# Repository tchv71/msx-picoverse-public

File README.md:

# PicoVerse for MSX

**The MSX experience driven by the Raspberry Pi Pico family of microcontrollers.**

PicoVerse is a community-driven effort to build versatile MSX cartridges powered by Raspberry Pi Pico development boards. The project pairs accessible hardware designs with ready-to-flash firmware so MSX users can jump straight into loading games, tools, and Nextor without having to compile sources.

| Cartridge Label - 2040 Variant | Cartridge Label - 2350 Variant |
|---------|---------|
| |  |

PicoVerse is designed as an open-source, independent, and documented MSX cartridge platform. Compatibility with other projects is neither a goal nor guaranteed (I tested some without much success); running third‑party software on PicoVerse hardware, or PicoVerse firmware on other boards, is at your own risk. The source and manufacturing files are openly available so you can learn, experiment, and build on them for the MSX community, subject to the project license.

If you find any issues, have questions, or want to contribute, please open an issue or reach out via the contact information in the repository.

## Project Highlights

- Single-ROM LoadROM workflow for instant and easy booting of one title.
- Multi-ROM loader with an on-screen menu and mapper auto-detection.
- Explorer firmware (PicoVerse 2350) merges flash and microSD ROMs, labels the source (FL/SD), adds MP3 playback, supports on-device search, includes ROM detail audio profiles with SCC/SCC+ and Dual PSG support, and includes an integrated File Hunter browser for downloading ROMs over ESP-01 WiFi.
- Ready-made Nextor builds with USB pendrive (`-s2`/`-m2`) or microSD card (`-s1`/`-m1`) via Sunrise IDE emulation on PicoVerse 2350, and USB (`-s`/`-m`) on PicoVerse 2040.
- Sunrise IDE + 192KB memory mapper on PicoVerse 2040 (`loadrom.exe -m`), or Sunrise IDE standalone (`loadrom.exe -s`).
- Sunrise IDE + 1MB PSRAM memory mapper on PicoVerse 2350 (`loadrom.exe -m1` for microSD, `loadrom.exe -m2` for USB), or Sunrise IDE standalone (`loadrom.exe -s1` / `loadrom.exe -s2`).
- Carnivore2-compatible RAM-mode loader on PicoVerse 2350 (`loadrom.exe -c1` / `loadrom.exe -c2`) for `SROM.COM /D15` uploads into the 1MB PSRAM mapper.
- ESP-01 WiFi support for PicoVerse 2350 Sunrise IDE LoadROM/MultiROM builds (`loadrom.exe -s1 -w`, `-m1 -w`, `-s2 -w`, `-m2 -w`) and for the Explorer File Hunter browser. Compatible with both real MSX hardware and FPGA-based MSX cores.
- SCC/SCC+, Dual PSG, and MSX-MUSIC/YM2413 emulation on the PicoVerse 2350, with per-ROM audio profile selection where supported.
- PC-side tooling that generates UF2 images locally for quick drag-and-drop flashing.
- USB keyboard support on PicoVerse 2040 — use a standard USB keyboard as the MSX keyboard via the cartridge slot.
- MSX-MIDI support on PicoVerse 2040 — use a USB-MIDI cable as a standard MSX-MIDI interface via the cartridge slot. 
- MIDI-PAC support on PicoVerse 2040 — passively convert live MSX PSG music and effects into high-quality MIDI for external synths or sound modules (SC-55 optimized). Features automatic bass detection, tone+noise coexistence, smooth pitch bending on fast passages, and improved percussion mapping. 
- USB joystick support on PicoVerse 2040 — plug a standard USB gamepad (HID, Xbox 360, Xbox One, or Xbox Series X|S) into the USB-C port and it appears as one or two native MSX joysticks with no MSX-side software needed. Uses open-drain bus driving to coexist with the real PSG.
- BOMs, and production-ready Gerbers.
- Active development roadmap covering RP2040 and RP2350-based cartridges.

## Documentation

**LoadROM Guides:** Use the LoadROM tool to create a UF2 image that boots directly into a single ROM, skipping the menu. Mapper type is auto-detected with filename tag overrides, and the tool reports the detected configuration before flashing.
- [MSX PicoVerse 2040 LoadROM Tool Manual (English)](/docs/msx-picoverse-2040-loadrom-tool-manual.en-us.md) 
- [MSX PicoVerse 2350 LoadROM Tool Manual (English)](/docs/msx-picoverse-2350-loadrom-tool-manual.en-us.md) 
  
**MultiROM Guides:** Use the MultiROM tool to create a UF2 image that allows selecting from multiple ROMs at boot. Mapper type is auto-detected with filename tag overrides, and the tool reports the detected configuration before flashing.
- [PicoVerse 2040 MultiROM Guide Manual (English)](/docs/msx-picoverse-2040-multirom-tool-manual.en-us.md)
- [PicoVerse 2350 MultiROM Tool Manual (English)](/docs/msx-picoverse-2350-multirom-tool-manual.en-us.md)

**Explorer Guides:** Use the Explorer tool to manage flash and microSD ROMs, play MP3s, browse File Hunter over ESP-01 WiFi, and search for titles on the device.
- [MSX PicoVerse 2350 Explorer Tool Manual (English)](/docs/msx-picoverse-2350-explorer-tool-manual.en-us.md)

**Reference Material** 
- [PicoVerse 2040 Features Overview](/docs/msx-picoverse-2040-features.md)
- [PicoVerse 2350 Features Overview](/docs/msx-picoverse-2350-features.md)
- [MSX PicoVerse 2350 Dual PSG Implementation](/docs/msx-picoverse-2350-dualpsg.md)
- [MSX PicoVerse 2350 MSX-MUSIC/FM-PAC Implementation](/docs/msx-picoverse-2350-fmpac.md)
- [MSX PicoVerse 2350 WiFi Support](/docs/msx-picoverse-2350-wifi.md)
- [MSX PicoVerse 2040 PIO Strategy](/docs/msx-picoverse-2040-pio.md) 
- [MSX PicoVerse 2350 PIO Strategy](/docs/msx-picoverse-2350-pio.md) 
- [MSX PicoVerse 2350 SCC Emulation](/docs/msx-picoverse-2350-scc.md)
- [MSX PicoVerse 2040 Sunrise IDE Emulation for Nextor](/docs/msx-picoverse-2040-sunrise-nextor.md) 
- [MSX PicoVerse 2350 Sunrise IDE Emulation for Nextor](/docs/msx-picoverse-2350-sunrise-nextor.md) 
- [MSX PicoVerse 2040 Mapper Implementation (Sunrise + Nextor)](/docs/msx-picoverse-2040-mapper.md) 
- [MSX PicoVerse 2040 USB Keyboard](/docs/msx-picoverse-2040-keyboard.md)
- [MSX PicoVerse 2040 MSX-MIDI](/docs/msx-picoverse-2040-msx-midi.md) 
- [MSX PicoVerse 2040 MIDI-PAC](/docs/msx-picoverse-2040-midipac.md)
- [MSX PicoVerse 2040 MegaROMs](/docs/msx-picoverse-2040-megaroms.md)
- [MSX PicoVerse 2040 USB Joystick](/docs/msx-picoverse-2040-joystick.md)

## Hardware Variants

### PicoVerse 2040 Cartridge

| Prototype PCB (front) | Prototype PCB (back) |
|---------|---------|
|  |  | 

- Based on RP2040 boards exposing 30 GPIO pins (not compatible with stock Raspberry Pi Pico pinout).
- Up to 16 MB of flash for MSX ROMs with support for Plain16/32 (`PLA-16`/`PLA-32`), Planar48/64 (`PLN-48`/`PLN-64`), Konami SCC, Konami, ASCII8/16/16X, NEO-8, NEO-16, and Manbow2 (`MANBW2`) mappers.
- USB-C port doubles as a bridge for Nextor mass storage via Sunrise IDE emulation (`loadrom.exe -s`).
- Sunrise IDE + 192KB memory mapper mode provides both Nextor disk access and expanded RAM (`loadrom.exe -m`).
- Standalone USB keyboard firmware — use a standard USB keyboard as the MSX keyboard via the cartridge slot (`loadrom.exe -k`). Not compatible with FPGA-based MSX systems or MSX computers with an integrated PPI (e.g. T9769 MSX-ENGINE).
- Standalone MSX-MIDI firmware — use a USB-MIDI cable as a standard MSX-MIDI interface for MIDI players and sequencers (`loadrom.exe -i`).
- Standalone MIDI-PAC firmware — passively listen to the MSX PSG and convert music and effects to USB MIDI for an external synth or sound module (`loadrom.exe -p`).
- Standalone USB joystick firmware — use a standard USB gamepad as an MSX joystick via the cartridge slot (`loadrom.exe -j`). Supports Xbox 360, Xbox One, Xbox Series X|S, and generic USB HID gamepads, with up to 2 gamepads mapped to MSX joystick ports 1 and 2.  Not compatible with FPGA-based MSX systems or MSX computers with an integrated PSG (e.g. T9769 MSX-ENGINE).

#### Bill of Materials

Interactive BOM available at [PicoVerse 2040 BOM](https://htmlpreview.github.io/?https://raw.githubusercontent.com/cristianoag/msx-picoverse-public/refs/heads/main/2040/hardware/MSX_PicoVerse_2040_1.3_bom.html)

| Reference | Description | Quantity | Link |
| --- | --- | --- | --- |
| U1 | RP2040 Dev Board 30 GPIO pins exposed | 1 | [AliExpress](https://s.click.aliexpress.com/e/_c4MuM9st) |
| C1 | 0603 0.1 µF Ceramic Capacitor | 1 | [AliExpress](https://s.click.aliexpress.com/e/_c2w5e36V) |
| C2 | 0603 10 µF Ceramic Capacitor | 1 | [AliExpress](https://s.click.aliexpress.com/e/_c2w5e36V)|
| R2, R3, R4, R5, R6, R7, R8, R9, R10, R11, R12, R13| 0603 10 kΩ Resistor | 12 | [AliExpress](https://s.click.aliexpress.com/e/_c3XBv4od)|
| R1 | 0603 2 KΩ Resistor | 1 | [AliExpress](https://s.click.aliexpress.com/e/_c3XBv4od)|
| D1 | 1N5819 SOD-123 Diode | 1 | [AliExpress](https://s.click.aliexpress.com/e/_c4WEKCuz) |
| Q1, Q2, Q3, Q4, Q5 | BSS138 SOT-23 Transistor | 5 | [AliExpress](https://s.click.aliexpress.com/e/_c2veWxcD)|

### PicoVerse 2350 Cartridge

| Prototype PCB (front) | Prototype PCB (back) |
|---------|---------|
|  |  |

- Targets RP2350 boards exposing all 48 GPIO pins (not compatible with standard Pico 2 boards).
- Adds microSD storage, ESP8266 WiFi header, and I2S audio expansion alongside 16 MB flash space.
- Extra RAM (PSRAM) now backs the 1MB mapper modes and the Carnivore2-compatible RAM loader, with room for additional advanced firmware features.
- Explorer firmware can load ROMs from both flash and microSD, browse File Hunter over ESP-01 WiFi, save downloaded File Hunter ROMs to the microSD root, search local title lists, and select SCC/SCC+ or Dual PSG audio profiles per ROM where supported.
- USB-C port doubles as a bridge for Nextor mass storage via Sunrise IDE emulation (`-s2`).
- microSD card slot provides Nextor mass storage via Sunrise IDE emulation (`-s1`).
- Sunrise IDE + 1MB PSRAM memory mapper mode provides both Nextor disk access and expanded RAM (`-m1` for microSD, `-m2` for USB).
- Carnivore2-compatible RAM-mode loading lets `SROM.COM /D15` upload ROMs into the 1MB PSRAM mapper (`-c1` for microSD, `-c2` for USB).
- LoadROM Sunrise builds can also expose ESP-01 WiFi support with `-w` on top of the `-s1`/`-m1`/`-s2`/`-m2` modes.
- Both LoadROM and MultiROM tools support the Sunrise IDE options; MultiROM allows combining them so multiple Nextor modes appear as selectable SYSTEM entries in the menu.
- Shares the same ROM mapper support list as the 2040 build.

#### Bill of Materials

Interactive BOM available at [PicoVerse 2350 BOM](https://htmlpreview.github.io/?https://raw.githubusercontent.com/cristianoag/msx-picoverse-public/refs/heads/main/2350/hardware/MSX_PicoVerse_2350_1.0-BETA_bom.html) 

| Reference | Description | Quantity | Link |
| --- | --- | --- | --- |
| U1 | WaveShare Core2350B Dev Board 48 GPIO pins exposed (8Mb PSRAM)| 1 | [AliExpress](https://pt.aliexpress.com/item/1005009578742534.html?spm=a2g0o.order_list.order_list_main.112.62b91802b6L8HW&gatewayAdapt=glo2bra) |
|U2| UDA1334A I2S Stereo DAC| 1 | [AliExpress](https://s.click.aliexpress.com/e/_c3gam5lH) |
|U3| ESP-01 ESP8266 WiFi Module| 1 | [AliExpress](https://s.click.aliexpress.com/e/_c4a5rnGj) |
|C1| 0603 0.1 µF Ceramic Capacitor | 1 | [AliExpress](https://s.click.aliexpress.com/e/_c3tkUxHz) |
|C2,C3| 0603 10 µF Ceramic Capacitor | 2 | [AliExpress](https://s.click.aliexpress.com/e/_c3tkUxHz)|
|R1| 0603 2 KΩ Resistor | 1 | [AliExpress](https://s.click.aliexpress.com/e/_c43uKcEj)|
|R2, R3, R6, R7, R8| 0603 10 kΩ Resistor | 4 | [AliExpress](https://s.click.aliexpress.com/e/_c43uKcEj)|
|R4, R5| 0603 5.1 kΩ Resistor | 2 | [AliExpress](https://s.click.aliexpress.com/e/_c43uKcEj)|
|R9, R10| 0603 330 Ω Resistor | 2 | [AliExpress](https://s.click.aliexpress.com/e/_c43uKcEj)|
|D1| 1N5819 SOD-123 Diode | 1 | [AliExpress](https://s.click.aliexpress.com/e/_c4WEKCuz) |
|SW1| Tactile Push Button Switch | 1 | [AliExpress](https://s.click.aliexpress.com/e/_c2IPGkzv) |
|J1| USB-C 16 Pin Connector | 1 | [AliExpress](https://s.click.aliexpress.com/e/_c4PtBc51) |
|J2| microSD Card Slot | 1 | [AliExpress](https://s.click.aliexpress.com/e/_c4Pzbd7Z) |

## Repository Contents
- `hardware/` – Production-ready Gerbers, fabrication notes, and BOMs for each supported dev board.
- `software/` – MultiROM PC utilities (`multirom.exe`) and menu ROM assets for both cartridge families.
- `docs/` – Feature lists, usage walkthroughs, and revision history for each cartridge family.
- `images/` – Board renders and build photos for quick identification.
- `labels/` – Printable Patola style cartridge label designs for both hardware variants.

## Quick Start
1. **Pick your target board**: Select the hardware revision that matches the RP2040 or RP2350 carrier you own, then grab the corresponding Gerber/BOM pack.
2. **Manufacture or assemble**: Send the Gerbers to your PCB house or build from an ordered kit. Follow the assembly notes included in each hardware bundle.
3. **Generate the UF2 image**:
   - For multiple titles, place your `.rom` files beside the MultiROM tool for your cartridge family (`2040/software/multirom.pio/tool/multirom.exe` or `2350/software/multirom.pio/tool/multirom.exe`) and run `multirom.exe` to create `multirom.uf2`.
   - For an instant boot into a single game, place the desired `.rom` next to the LoadROM tool for your cartridge family and run `loadrom.exe <file> [-o custom.uf2]` to create a dedicated UF2 that skips the menu.
   - For a combined flash + microSD menu (on PicoVerse 2350 only), use the Explorer tool (`2350/software/explorer.pio/tool/explorer.exe`) to create `explorer.uf2`, then copy extra `.rom` and `.mp3` files to the microSD card. With an ESP-01 module and configured WiFi, Explorer can also browse File Hunter and save downloaded ROMs directly to the microSD root.
4. **Flash the firmware**:
   - Hold BOOTSEL while connecting the cartridge to your PC via USB-C.
   - Copy the freshly generated UF2 (`multirom.uf2`, `loadrom.uf2`, or `explorer.uf2`) to the RPI-RP2 drive that appears.
   - Eject the drive; the board reboots and stores the image in flash.
5. **Enjoy on MSX**: Insert the cartridge, power on the computer, pick a ROM from the menu, or launch Nextor to access USB or microSD storage.

## MultiROM Menu

| PicoVerse 2040 MultiRom | PicoVerse 2350 MultiRom |
|---------|---------|
|||

To use the MultiROM menu, insert the PicoVerse cartridge into your MSX and power it on. The system will boot directly into the MultiROM menu, which displays a list of all ROMs embedded in the cartridge. Each entry is named after the ROM filename (up to 50 characters), and longer names are shown using a scrolling effect.

Navigate the menu using the keyboard arrow keys. Use the Up and Down keys to move through the list of ROMs, and if more than 19 ROMs are present, use the Left and Right keys to switch between pages. To start a game or application, select it and press Enter or Space; the MSX will boot the ROM using the appropriate mapper configuration automatically.

While in the menu, pressing the H key opens a help screen with basic instructions; press any key to return to the main menu. Once a ROM is launched, control is handed over entirely to the selected software, just as if it were a physical cartridge inserted into the MSX.

Check the detailed MultiROM guide in the documentation folder for advanced features, troubleshooting tips, and mapper support details.

## LoadROM Tool

The LoadROM tool targets situations where you want the PicoVerse to behave like a traditional single-game cartridge or as a dedicated standalone firmware image. Instead of showing the MultiROM menu, the Pico boots straight into one ROM embedded in the UF2 image, or into a selected standalone mode such as keyboard, MSX-MIDI, MIDI-PAC, or USB joystick.

- **Input**: exactly one `.ROM` file. Mapper type is auto-detected with the same heuristics as MultiROM, and you can still force a mapper via filename tags such as `.KonSCC.ROM` or `.PLA-32.ROM`.
- **Output**: `loadrom.uf2` by default, or any filename you pass via `-o`. The UF2 contains the firmware, a 59-byte configuration record (title, mapper, size, flash offset), and the ROM payload.
- **Workflow**:
   1. Open a Command Prompt or PowerShell window in your target package folder:
      - `2040/software/loadrom.pio/tool`, or
      - `2350/software/loadrom.pio/tool`.
   2. Run `loadrom.exe -o mygame.uf2 \\path\\to\\Game.ROM` (the tool also accepts drag-and-drop onto the EXE).
      - MSX-MIDI standalone mode: `loadrom.exe -i -o midi.uf2`
      - MIDI-PAC standalone mode: `loadrom.exe -p -o midipac.uf2`
      - USB joystick standalone mode: `loadrom.exe -j -o joystick.uf2`
      - SCC standard emulation (only PicoVerse 2350): `loadrom.exe -scc \\path\\to\\Game.ROM`
      - SCC+ enhanced emulation (only PicoVerse 2350): `loadrom.exe -sccplus \\path\\to\\Game.ROM`
      - MSX-MUSIC/FM-PAC emulation with the bundled English FM-PAC BIOS (only PicoVerse 2350, non-SYSTEM ROMs): `loadrom.exe -f \\path\\to\\Game.ROM`, `loadrom.exe -fmpac \\path\\to\\Game.ROM`, or `loadrom.exe --fmpac -o mygame-fmpac.uf2 \\path\\to\\Game.ROM`
      - Dual PSG emulation on secondary PSG ports `0x10`/`0x11` (only PicoVerse 2350, supported non-SYSTEM ROMs): `loadrom.exe -d \\path\\to\\Game.ROM` or `loadrom.exe --dual-psg -o mygame-dualpsg.uf2 \\path\\to\\Game.ROM`
      - `-scc` and `-sccplus` are mutually exclusive.
      - `-scc`, `-sccplus`, `-f` / `-fmpac`, and `-d` / `--dual-psg` are cartridge audio modes; use only one of them per UF2.
      - `-f` / `-fmpac` is not valid with Sunrise or Carnivore2 system modes (`-s1`, `-m1`, `-s2`, `-m2`, `-c1`, or `-c2`) or with Konami SCC / Manbow2 mapper ROMs.
      - `-d` / `--dual-psg` is intended for software that writes to a second PSG. It is not available for Konami SCC or Manbow2 mapper ROMs, SCC/SCC+ audio builds, Sunrise/Nextor system modes, or Carnivore2 system modes.
      - Sunrise IDE standalone (PicoVerse 2040): `loadrom.exe -s`
      - Sunrise IDE + 192KB mapper (PicoVerse 2040): `loadrom.exe -m`
      - Sunrise IDE standalone (PicoVerse 2350): `loadrom.exe -s1` or `loadrom.exe -s2`
      - Sunrise IDE + 1MB PSRAM mapper (PicoVerse 2350): `loadrom.exe -m1` or `loadrom.exe -m2`
      - Sunrise IDE + WiFi (PicoVerse 2350): `loadrom.exe -s1 -w`, `loadrom.exe -s2 -w`, `loadrom.exe -m1 -w`, or `loadrom.exe -m2 -w`
      - Carnivore2-compatible RAM loader (PicoVerse 2350): `loadrom.exe -c1` or `loadrom.exe -c2`
      - `-w` is currently supported only with `-s1`, `-m1`, `-s2`, or `-m2`.
   3. Observe the reported ROM name, size, mapper status (auto vs forced), and Pico offset before the UF2 is written.
   4. Put the Pico into BOOTSEL mode and copy the generated UF2 to the `RPI-RP2` drive.
   5. Insert the cartridge into your MSX—on power-up the embedded game launches immediately.

Consult the LoadROM manuals linked above for screenshots, troubleshooting, and in-depth explanations of mapper forcing, UF2 structure, and limitations.

## Explorer Firmware (RP2350)

|Explorer Flash Menu|Explorer MicroSD Menu|
|---|---|
|||
|<center>**File Hunter Explorer Menu**|<center>**WiFi Configuration Screen**|
|||

Explorer is a PicoVerse 2350-only firmware that merges ROMs stored in flash with additional ROMs and MP3 files on the microSD card. ROMs are labeled with source tags (FL/SD), MP3 entries open a player screen, the list supports paging, and you can search by name directly in the menu. With an ESP-01 / ESP8266 module installed and WiFi configured, pressing `F3` opens the integrated File Hunter browser. File Hunter results show the ROM name and size, can be searched from the MSX, and selected ROMs are downloaded through the Pico into PSRAM before being saved as `.ROM` files in the microSD root. microSD ROMs up to 2 MB can be executed directly from there. Use the Explorer tool to build the UF2 and copy extra ROMs and MP3 files to the microSD card. See the Explorer manual for limits (flash vs SD capacity, 2 MB SD ROM limit, File Hunter requirements, and supported formats).

You can have up to 1024 entries per folder view (folders + ROMs + MP3s; the root view can also include flash entries). The menu auto-detects whether the MSX supports 80-column text mode and boots accordingly; you can also press `C` at any time to toggle between 40- and 80-column layouts.

Explorer ROM entries open a detail screen where you can inspect mapper detection and choose a cartridge audio profile. For supported non-SYSTEM ROMs, select **Dual PSG** and run the ROM to enable the second cartridge-side PSG on ports `0x10` and `0x11`. Explorer hides or rejects Dual PSG where the second cartridge audio slot is reserved, including Konami SCC, Manbow2, SYSTEM entries, folders, and File Hunter folder records. 

A search function is available by pressing `/` in the menu. Type part of a ROM name and press Enter to jump to the first matching entry. Press `H` to view the help screen.

The File Hunter browser was implemented with reference to NataliaPC's public MSX File Hunter Browser project: https://github.com/nataliapc/msx_filehunterbrowser

## Compatibility & Requirements

- Works with MSX, MSX2, MSX2+, and MSX TurboR systems. Mapper support covers the most common game and utility formats.
- Requires Windows OS to run the PC-side UF2 builder utilities.
- Ensure your development board matches the pinout documented for each hardware revision before soldering.

## License, Copyright notes & Usage

All hardware and firmware binaries in this repository are released under the Creative Commons Attribution-NonCommercial-ShareAlike 4.0 International license. Personal builds and community tinkering are encouraged, but **commercial use or resale requires explicit authorization from the author**.

**bios.h** is used on all MSX menus and was adapted from http://www.konamiman.com/msx/msx2th/th-ap.txt by Danilo Angelo, 2020. The original file is licensed under CC0 1.0 Universal (public domain). The adapted bios.h file in this repository is also released under CC0 1.0 Universal, allowing for free use and modification without restrictions.

**msxromcrt0.s** is used on Nextor C implementation and was adapted by S0urceror, 2022, from the crt0.s file available in FusionC v2.0. The original crt0.s file is licensed under the MIT License. The adapted msxromcrt0.s file in this repository is also released under the MIT License, permitting free use, modification, and distribution with proper attribution.

**uf2format.h** is used in all UF2 builder tools and was adapted from the UF2 specification and reference implementation available at https://github.com/Microsoft/uf2/blob/master/uf2.h. The original uf2.h is copyright by Microsoft Corp and the file is licensed under the MIT License. The adapted uf2format.h file in this repository is also released under the MIT License, allowing for free use, modification, and distribution with proper attribution.

**emu2212.c** and **emu2212.h** used to implement SCC and SCC+ emulation are copyright by Mitsutaka Okazaki 2014 and licensed under the MIT License, allowing for free use, modification, and distribution with proper attribution. [emu2212 @ Digital Sound Antiques](https://github.com/digital-sound-antiques/emu2212)

**emu2149.c** and **emu2149.h** used to implement AY-3-8910 emulation/dual PSG feature are copyright by Mitsutaka Okazaki 2014 and licensed under the MIT License, allowing for free use, modification, and distribution with proper attribution. [emu2149 @ Digital Sound Antiques](https://github.com/digital-sound-antiques/emu2149)

**emu2413.c** and **emu2413.h** used to implement YM2413 / MSX-MUSIC emulation are copyright by Mitsutaka Okazaki 2020 and licensed under the MIT License, allowing for free use, modification, and distribution with proper attribution. [emu2413 @ Digital Sound Antiques](https://github.com/digital-sound-antiques/emu2413)

**FMPCCMFC.BIN** is the English FM-PAC BIOS used by PicoVerse 2350 LoadROM when `-f` / `-fmpac` is selected. The FM-PAC BIOS ROM is copyrighted by Matsushita Corp.; the English translation is credited to 232, Max Iwamoto, and GDX.

**MIDI-PAC PSG-to-MIDI Conversion:**  
The MIDI-PAC firmware and its quality improvements were developed against public technical references and behavior studies. The PSG-to-MIDI mapping combines hardware-correct AY-3-8910 / YM2149 interpretation with pragmatic General MIDI reinterpretation for musical output on modules like the Roland SC-55. Key references used include:  
- The `berarma/aymidi` project by berarma (AY-3-8910 to MIDI conversion reference).  
- The `ayumi` AY/YM2149 emulator by Peter Sovietov (Peter Sovietov, 2022; used for envelope generation verification).  
- The ESEMSX3 FPGA implementation `midi.vhd` (serves as a minimal alternative PSG-to-MIDI transport reference).  
- AY-3-8910 and YM2149 datasheets and hardware behavior documentation (General Instruments and Yamaha specifications).  
- MSX-MIDI specification and USB MIDI 1.0 Event Packet format (USB Implementers Forum).  
- The Sunrise IDE specification and Nextor protocol documentation.  

These references informed structure, timing, envelope shapes, and musical mapping decisions. The PicoVerse firmware maintains its own implementation with no dependencies on external emulation libraries. The PicoVerse files are licensed under CC BY-NC-SA 4.0, allowing for non-commercial use and modification with proper attribution, but commercial use or resale requires explicit authorization from the author.

**MSX-MIDI Interface:**  
The MSX-MIDI firmware was developed using the MSX-MIDI specification, USB MIDI 1.0 specification, TinyUSB host API, and reference behavior from ESEMSX3 and similar implementations. The 8251 USART emulation and standard MIDI wire protocol handling are original PicoVerse implementations.

**The Sunrise IDE driver for Nextor** used on PicoVerse is copyright by Konamiman, Piter Punk, and FRS, and is licensed under the special terms by MSX Licensing Corporation. The original Sunrise IDE code is available at https://github.com/Konamiman/Nextor/blob/v2.1/source/kernel/drivers/SunriseIDE/sunride.asm

The algorithm to emulate ATA devices is original and based on the implementation for the Carnivore2 cartridge, Copyright (c) 2017-2024 by the RBSC group. Portions (c) Mitsutaka Okazaki and (c) Kazuhiro Tsujikawa. Available at https://github.com/RBSC/Carnivore2/tree/master/Firmware/Sources

**WiFi support on PicoVerse 2350** was implemented with direct reference to the ESP8266 / MSX WiFi work by Oduvaldo Pavan Junior (`ducasp`). The PicoVerse WiFi ROM integration, memio register layout, fixed-`859372` UART behavior, FIFO clear command handling, quick-receive behavior, and ESP-side protocol compatibility were based on public source and documentation from Oduvaldo's projects. Important references used include:
- `MSXPICO/UNAPI_BIOS_CUSTOM_ESP_MSXPICO/ESP8266_memio.asm` from `ducasp/MSX-Development` for the memory-mapped ROM and register model.
- `MSX-SM/WiFi/UNAPI_BIOS_CUSTOM_ESP_FIRMWARE` and related WiFi utilities from `ducasp/MSX-Development` for the ROM/driver lineage and behavior.
- `ducasp/ESP8266-UNAPI-Firmware` and its documentation for the serial protocol, command/response structure, and ESP firmware behavior.

Those projects remain copyright by Oduvaldo Pavan Junior and their respective contributors under their original terms. PicoVerse reuses the public technical design references and keeps its own RP2350 cartridge-side implementation.

**File Hunter browser integration on PicoVerse 2350 Explorer** was implemented with reference to NataliaPC's MSX File Hunter Browser project and the public File Hunter service behavior. PicoVerse keeps its own Explorer MSX menu and RP2350/ESP8266 transport implementation, while acknowledging the original MSX File Hunter Browser code and workflow by NataliaPC. Reference repository: https://github.com/nataliapc/msx_filehunterbrowser

**Mapper detection heuristics and filename tag forcing schemes** in the LoadROM and MultiROM tools are original implementations by the OpenMSX developers for the Romfactory module and licensed under the GNU Public License (GPL). Available at https://github.com/openMSX/openMSX/blob/6f8aa9865eeccdb0b31043d8851b822538440204/src/memory/RomFactory.cc

**The softwaredb database** used for ROM mapper detection is built upon contributions from across the MSX community, including the initial work by Nicolas Beyaert, later expanded by the BlueMSX Team (2004–2013) and continuously maintained by the openMSX Team (2005–present). It also incorporates MSX ID data generated by Generation MSX (www.generation-msx.nl). Special thanks go to the Generation MSX / Sylvester project for its extensive reference data, as well as to contributors such as p_gimeno and diedel for ROM additions and validation, and GDX for further ROM information, corrections, and verification efforts. Part of OpenMSX effort. Available at https://github.com/openMSX

## Feedback & Community

Questions, test reports, and build photos are welcome. Open an issue on the public repository or reach out through the MSX retro hardware forums where PicoVerse updates are posted.

Author: Cristiano Goncalves
Last updated: 05/17/2026

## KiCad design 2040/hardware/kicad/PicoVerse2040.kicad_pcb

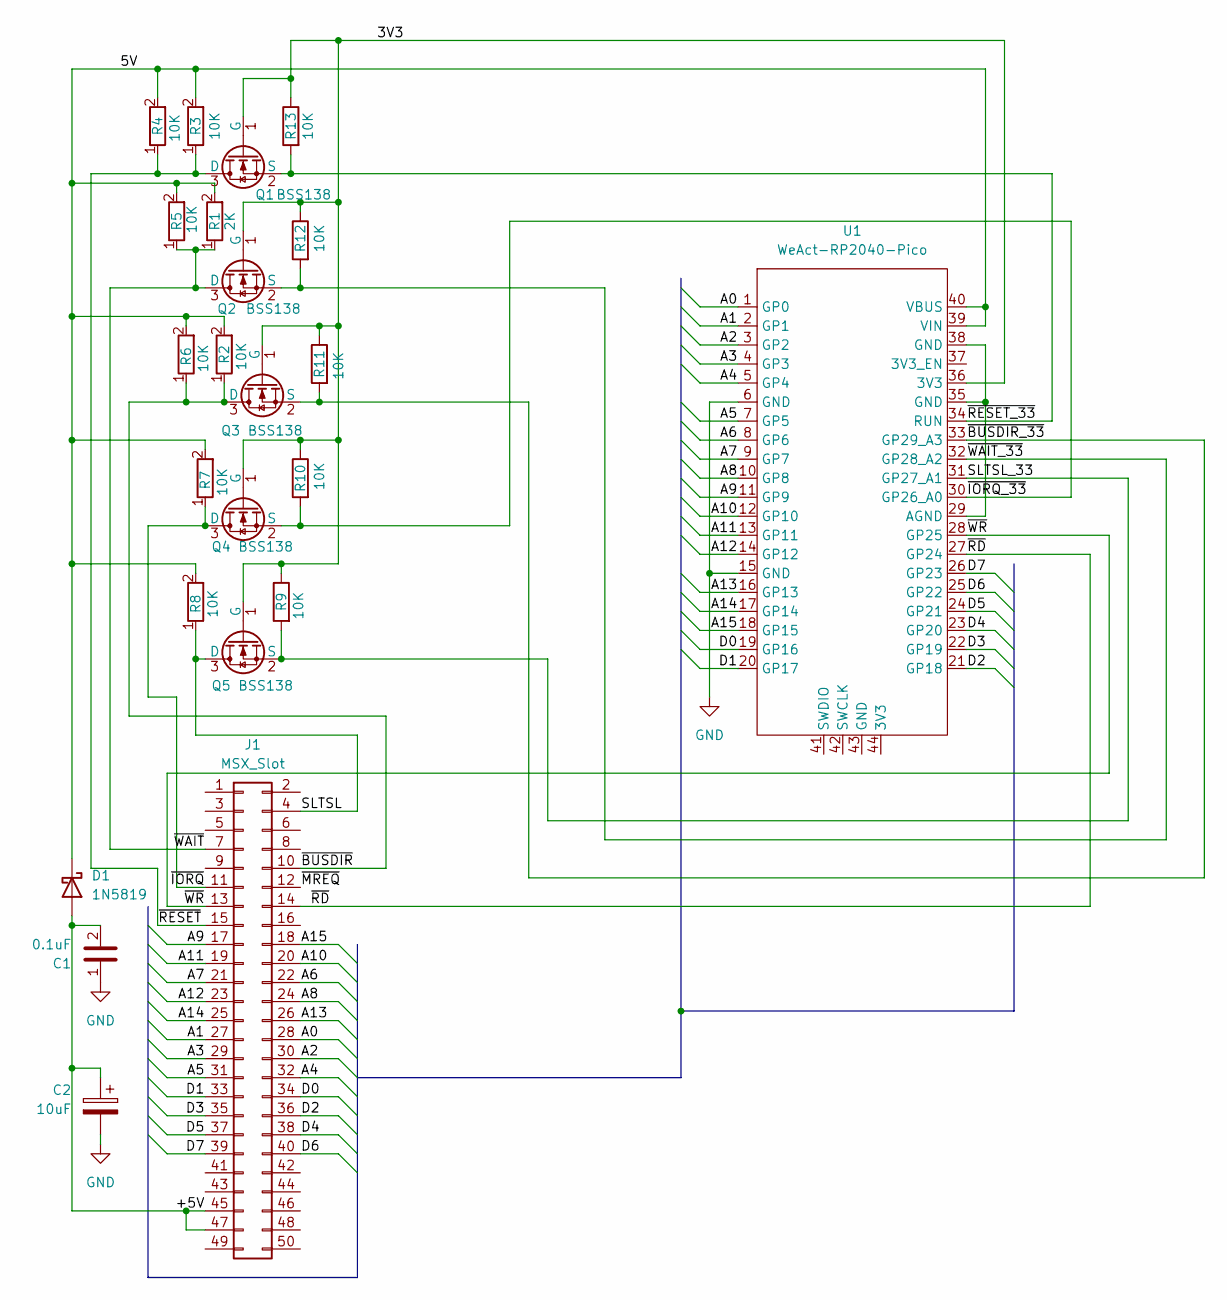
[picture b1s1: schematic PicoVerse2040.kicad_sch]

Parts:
C1: 0.1uF; C_0603_1608Metric_Pad1.08x0.95mm_HandSolder
C2: 10uF; C_0603_1608Metric_Pad1.08x0.95mm_HandSolder
D1: 1N5819; D_SOD-123
J1: MSX_Slot
Q1, Q2, Q3, Q4, Q5: BSS138; SOT-23
R1: 2K; R_0603_1608Metric
R2, R3, R4, R5, R6, R7, R8, R9, R10, R11, R12, R13: 10K; R_0603_1608Metric_Pad0.98x0.95mm_HandSolder
U1: WeAct-RP2040-Pico; RaspberryPi_Pico_Common_THT

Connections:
/3V3: Q1.1 (G), Q2.1 (G), Q3.1 (G), Q4.1 (G), Q5.1 (G), R9.1, R10.1, R11.1, R12.1, R13.1, U1.36 (3V3)
/5V: D1.1 (K), R1.2, R2.2, R3.2, R4.2, R5.2, R6.2, R7.2, R8.2, U1.39 (VIN), U1.40 (VBUS)
/+5V: C1.2, C2.1, D1.2 (A), J1.45, J1.47
/A0: J1.28, U1.1 (GP0)
/A1: J1.27, U1.2 (GP1)
/A2: J1.30, U1.3 (GP2)
/A3: J1.29, U1.4 (GP3)
/A4: J1.32, U1.5 (GP4)
/A5: J1.31, U1.7 (GP5)
/A6: J1.22, U1.8 (GP6)
/A7: J1.21, U1.9 (GP7)
/A8: J1.24, U1.10 (GP8)
/A9: J1.17, U1.11 (GP9)
/A10: J1.20, U1.12 (GP10)
/A11: J1.19, U1.13 (GP11)
/A12: J1.23, U1.14 (GP12)
/A13: J1.26, U1.16 (GP13)
/A14: J1.25, U1.17 (GP14)
/A15: J1.18, U1.18 (GP15)
/D0: J1.34, U1.19 (GP16)
/D1: J1.33, U1.20 (GP17)
/D2: J1.36, U1.21 (GP18)
/D3: J1.35, U1.22 (GP19)
/D4: J1.38, U1.23 (GP20)
/D5: J1.37, U1.24 (GP21)
/D6: J1.40, U1.25 (GP22)
/D7: J1.39, U1.26 (GP23)
/SLTSL: J1.4, Q5.3 (D), R8.1
/SLTSL_33: Q5.2 (S), R9.2, U1.31 (GP27_A1)
/~BUSDIR_33: Q3.2 (S), R11.2, U1.33 (GP29_A3)
/~BUSDIR: J1.10, Q3.3 (D), R2.1, R6.1
/~IORQ_33: Q4.2 (S), R10.2, U1.30 (GP26_A0)
/~IORQ: J1.11, Q4.3 (D), R7.1
/~RD: J1.14, U1.27 (GP24)
/~RESET_33: Q1.2 (S), R13.2, U1.34 (RUN)
/~RESET: J1.15, Q1.3 (D), R3.1, R4.1
/~WAIT_33: Q2.2 (S), R12.2, U1.32 (GP28_A2)
/~WAIT: J1.7, Q2.3 (D), R1.1, R5.1
/~WR: J1.13, U1.28 (GP25)
GND: C1.1, C2.2, U1.6 (GND), U1.15 (GND)
unnamed: U1.29 (AGND), U1.35 (GND), U1.38 (GND)

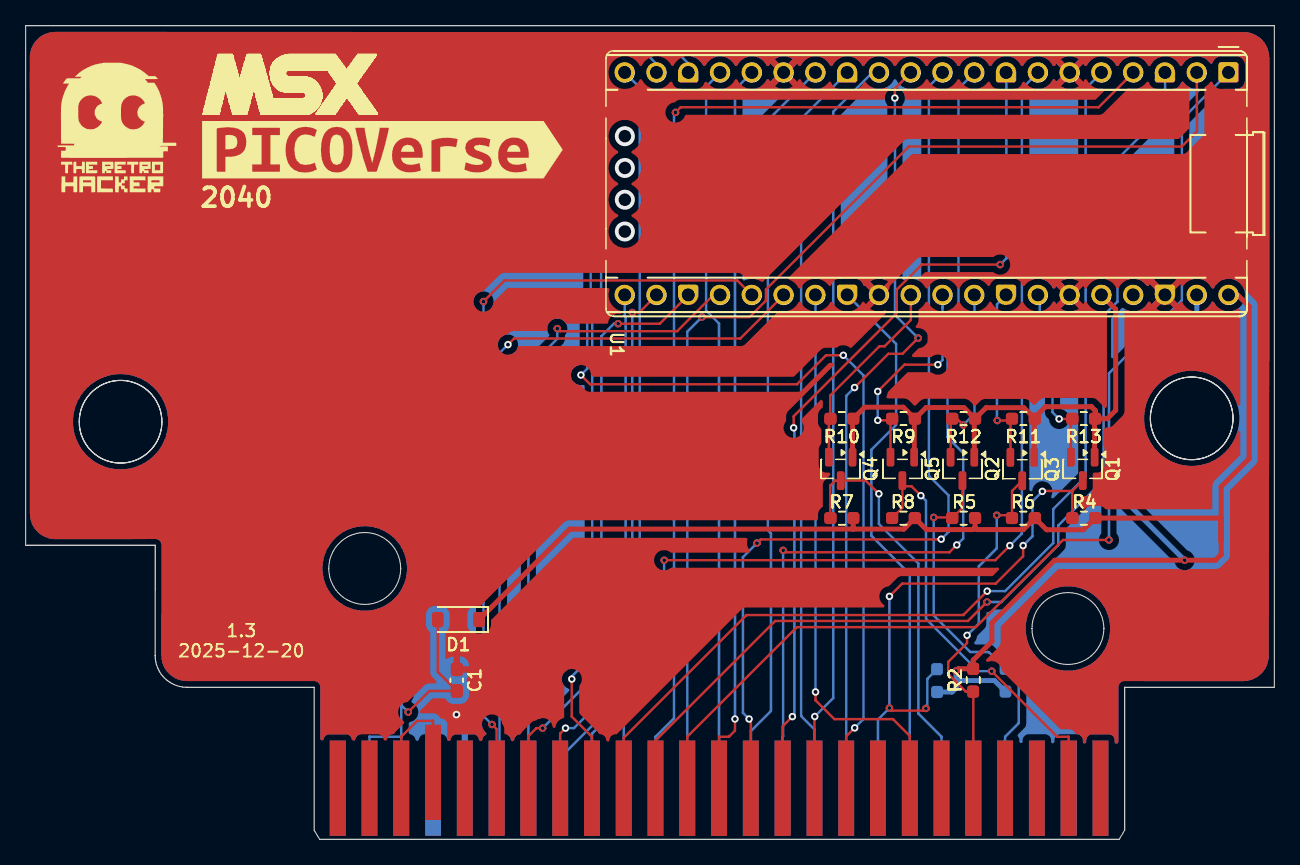
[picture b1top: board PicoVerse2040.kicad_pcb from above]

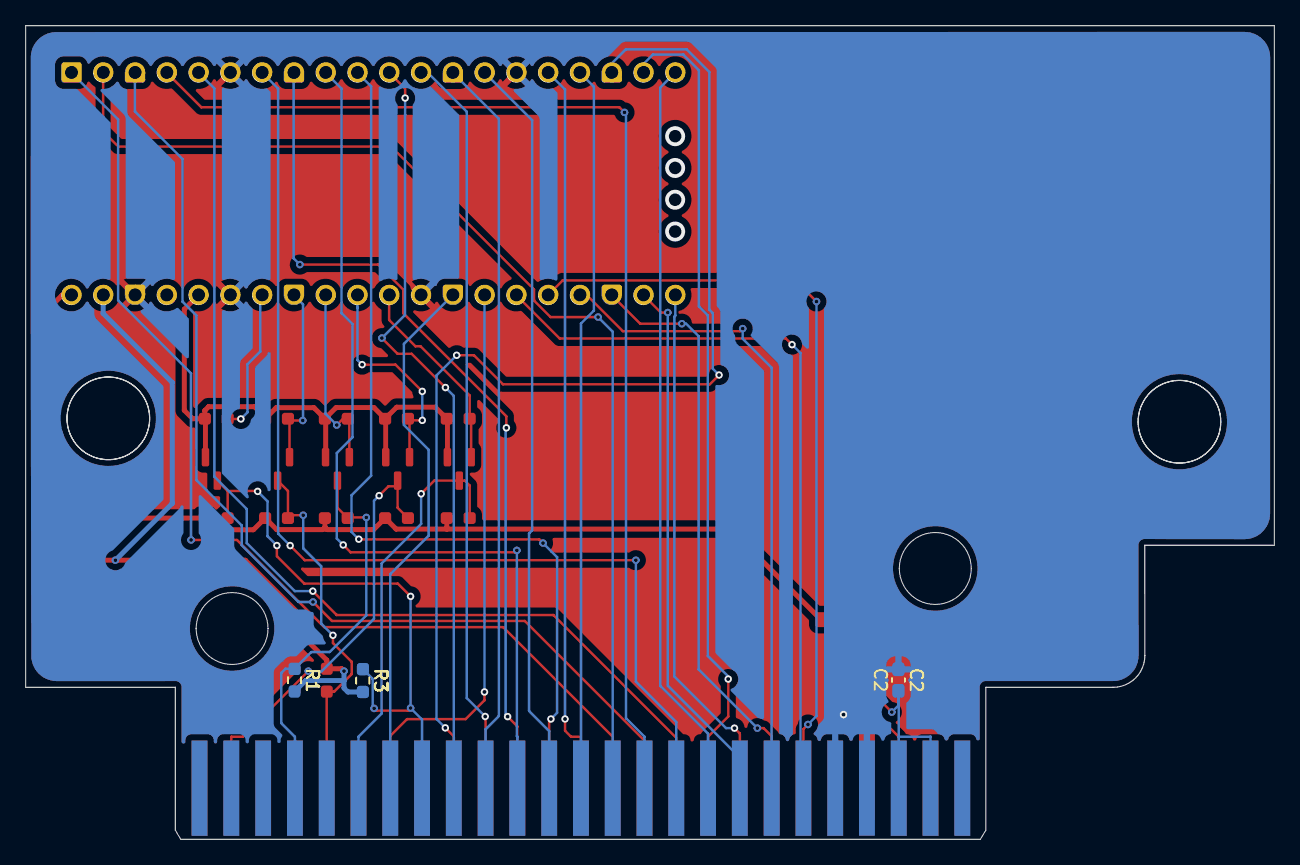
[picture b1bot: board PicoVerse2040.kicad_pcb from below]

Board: 2 copper layers, 99.8 x 65.0 mm, 22 parts (3 on the bottom side), 15 nets.

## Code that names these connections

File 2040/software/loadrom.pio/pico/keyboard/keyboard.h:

// MSX PICOVERSE PROJECT
// (c) 2026 Cristiano Goncalves
// The Retro Hacker
//
// keyboard.h - Pin definitions and constants for MSX PicoVerse USB Keyboard firmware
//
// This work is licensed under a "Creative Commons Attribution-NonCommercial-ShareAlike 4.0 International
// License". https://creativecommons.org/licenses/by-nc-sa/4.0/

#ifndef KEYBOARD_H
#define KEYBOARD_H

// -----------------------------------------------------------------------
// GPIO pin assignments (directly mapped to MSX bus signals)
// -----------------------------------------------------------------------
// Address lines (A0-A15)
#define PIN_A0     0
#define PIN_A1     1
#define PIN_A2     2
#define PIN_A3     3
#define PIN_A4     4
#define PIN_A5     5
#define PIN_A6     6
#define PIN_A7     7
#define PIN_A8     8
#define PIN_A9     9
#define PIN_A10    10
#define PIN_A11    11
#define PIN_A12    12
#define PIN_A13    13
#define PIN_A14    14
#define PIN_A15    15

// Data lines (D0-D7)
#define PIN_D0     16
#define PIN_D1     17
#define PIN_D2     18
#define PIN_D3     19
#define PIN_D4     20
#define PIN_D5     21
#define PIN_D6     22
#define PIN_D7     23

// Control signals
#define PIN_RD     24   // /RD   — active-low read strobe
#define PIN_WR     25   // /WR   — active-low write strobe
#define PIN_IORQ   26   // /IORQ — active-low I/O request
#define PIN_SLTSL  27   // /SLTSL — active-low slot select (unused by keyboard)
#define PIN_WAIT   28   // /WAIT  — active-low, driven by PIO to freeze Z80 during I/O reads
#define PIN_BUSDIR 29  // BUSSDIR — bus direction control (unused by keyboard)

#define PICO_FLASH_SPI_CLKDIV 2

#endif

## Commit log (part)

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2026-05-18 - Removed Konami SCC and Manbow2 from the supported MSX-MUSIC/FM-PAC mapper set; the LoadROM tool now rejects `-f` / `-fmpac` for those ROMs and the firmware FM-PAC wrapper no longer carries SCC-clas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
2026-05-22 Update kicad
2026-05-22 Revert "Merge branch 'main' of https://github.com/tchv71/msx-picoverse-public"
    This reverts commit a3ed62548e82abeba98711e7134bc43e69b952c0, reversing
    changes made to 5d39053092ba99a309041cc20d9bcc0b0da891bb.
2026-05-26 Fix MREQ <-> IORQ
2026-05-26 Fix bugs
2026-05-26 Fix reading from memory and ports
2026-06-10 Fix pcb
2026-06-15 Intermediate
2026-06-16 Intermediate 2
2026-06-16 Move monz80 window to 0x8000
2026-06-19 Working
2026-06-21 Working 2
